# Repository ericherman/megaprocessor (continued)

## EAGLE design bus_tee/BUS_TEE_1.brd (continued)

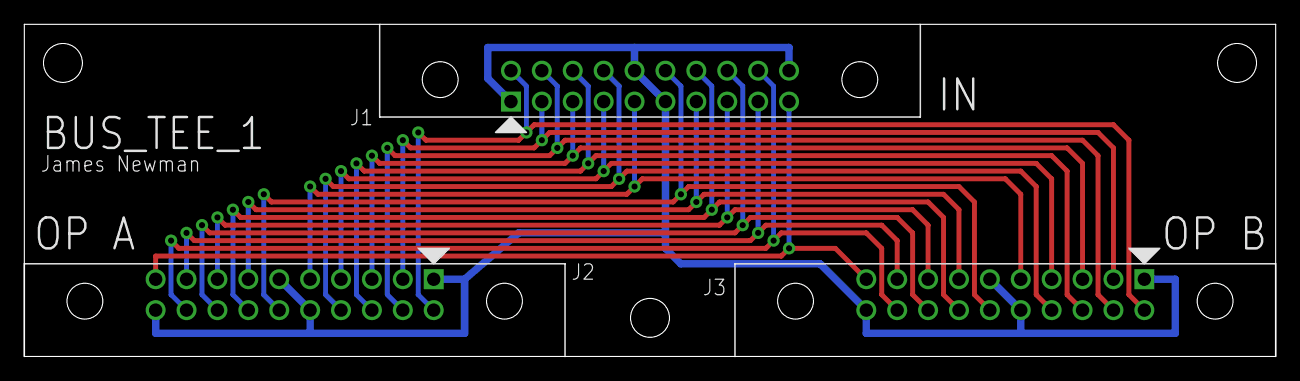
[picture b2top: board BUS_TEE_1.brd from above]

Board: 2 copper layers, 102.9 x 27.3 mm, 6 parts (0 on the bottom side), 17 nets.

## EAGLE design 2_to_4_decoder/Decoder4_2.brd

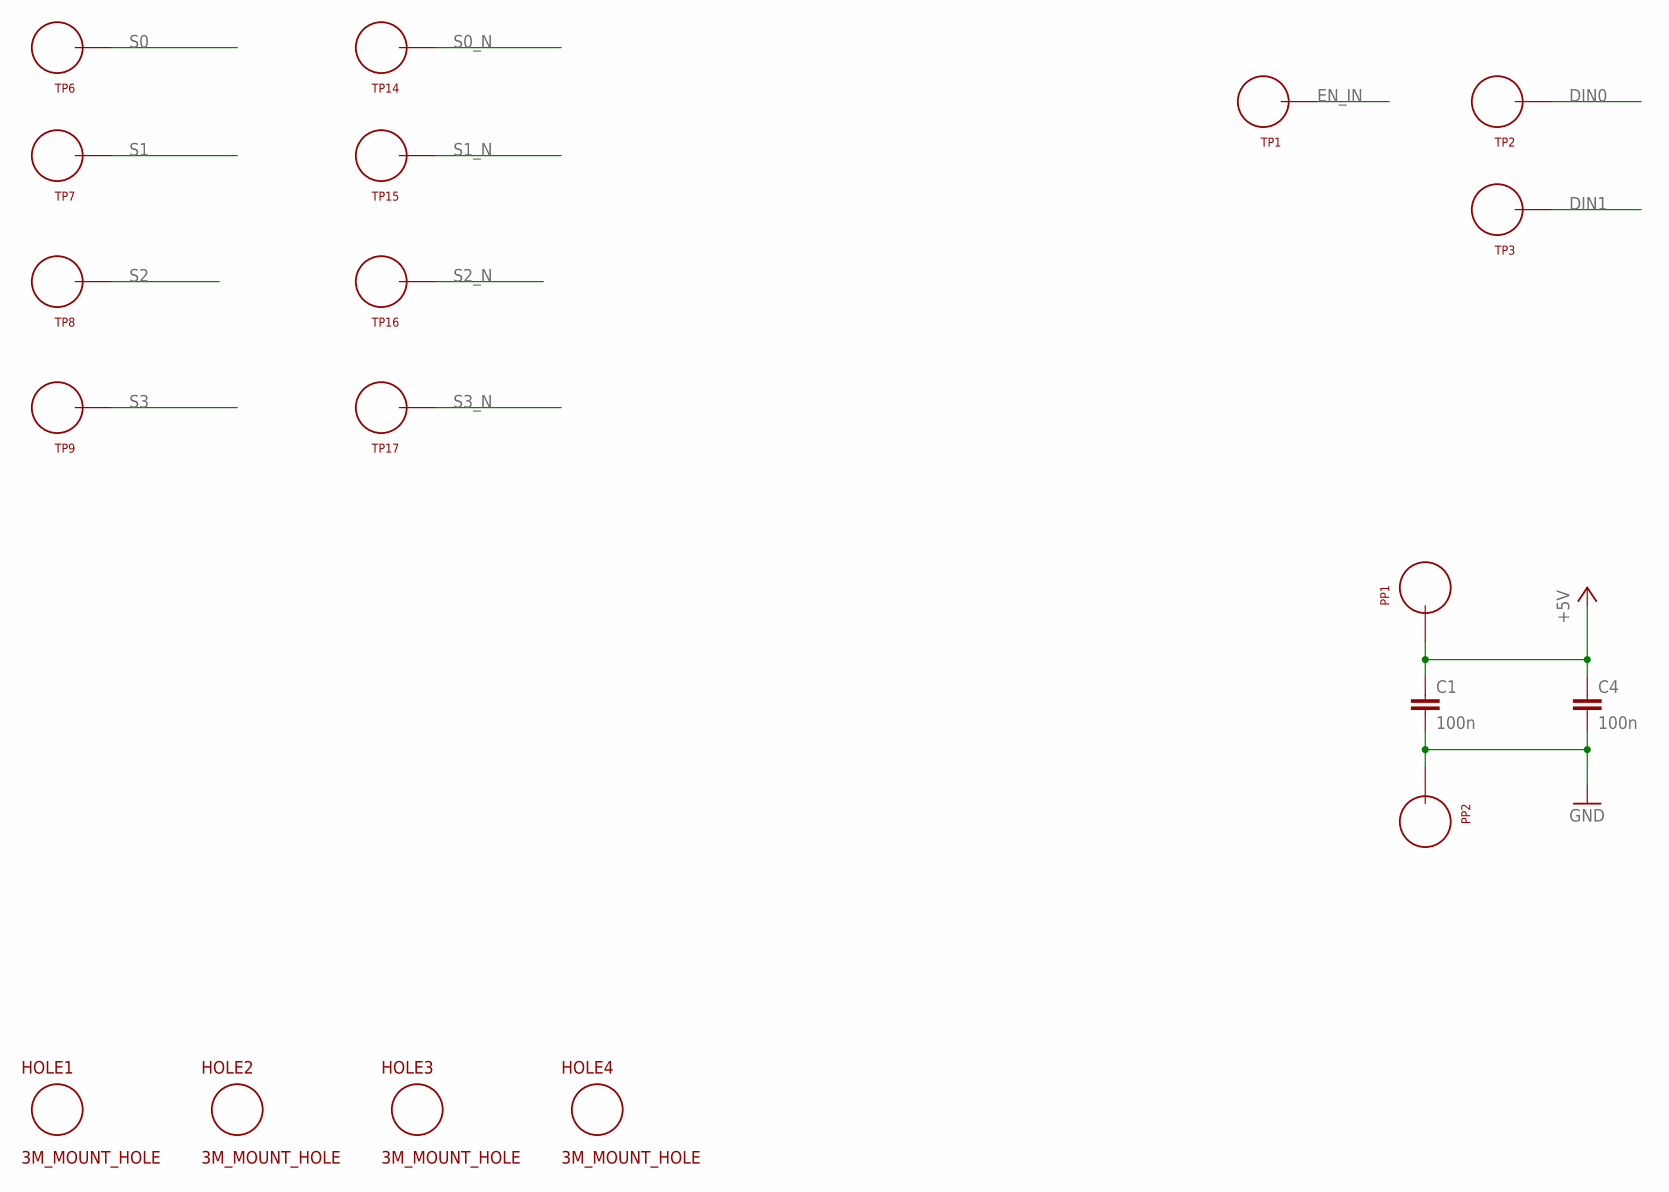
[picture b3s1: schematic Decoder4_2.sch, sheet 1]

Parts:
C1, C4: 100n; CAP_P2INCH
HOLE1, HOLE2, HOLE3, HOLE4: 3M_MOUNT_HOLE; 3M_HOLE
PP1, PP2: TEST_LOOP
TP1, TP2, TP3, TP6, TP7, TP8, TP9, TP14, TP15, TP16, TP17: TEST_LOOP

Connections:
+5V: C1.1, C4.1, PP1.P$1; also elsewhere on the board
DIN0: TP2.P$1; also elsewhere on the board
DIN1: TP3.P$1; also elsewhere on the board
EN_IN: TP1.P$1; also elsewhere on the board
GND: C1.2, C4.2, PP2.P$1; also elsewhere on the board
S0: TP6.P$1; also elsewhere on the board
S0_N: TP14.P$1; also elsewhere on the board
S1: TP7.P$1; also elsewhere on the board
S1_N: TP15.P$1; also elsewhere on the board
S2: TP8.P$1; also elsewhere on the board
S2_N: TP16.P$1; also elsewhere on the board
S3: TP9.P$1; also elsewhere on the board
S3_N: TP17.P$1; also elsewhere on the board

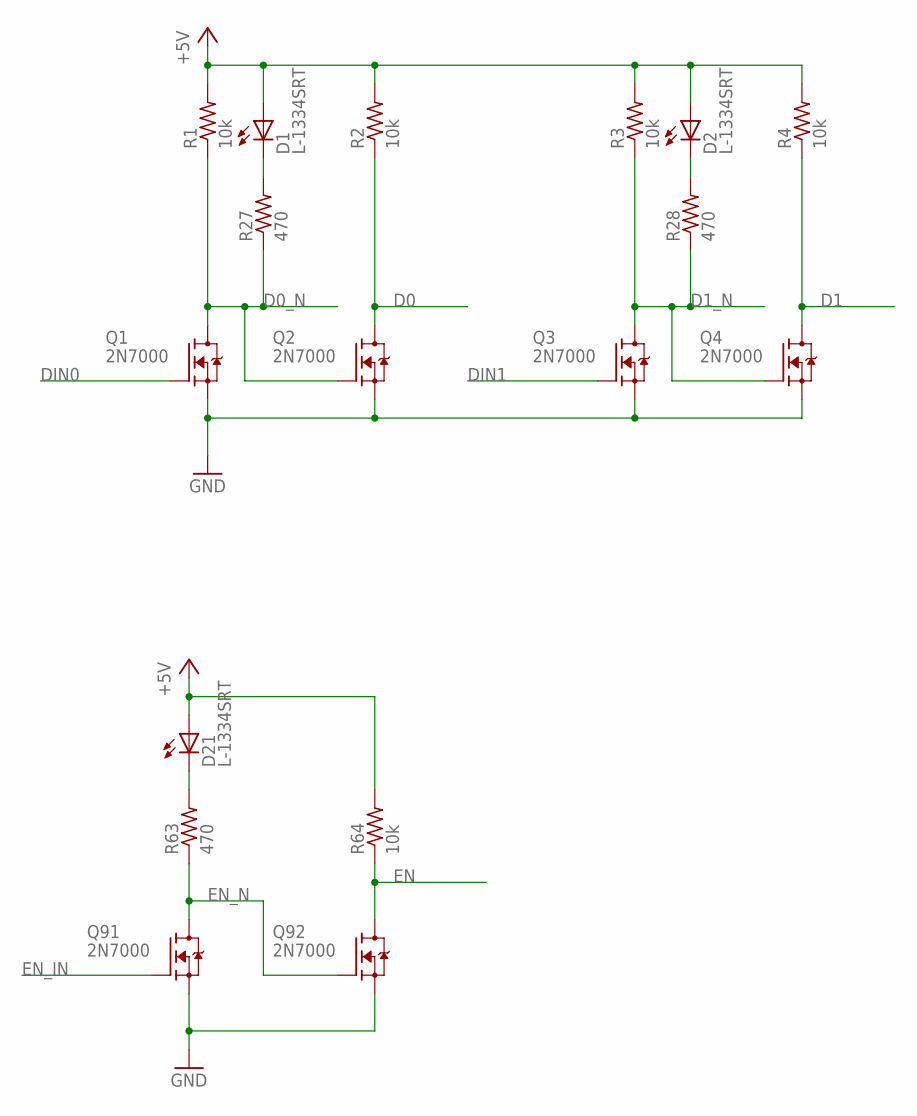
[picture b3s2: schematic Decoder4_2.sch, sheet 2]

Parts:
D1, D2, D21: L-1334SRT; LED3MM
Q1, Q2, Q3, Q4, Q91, Q92: 2N7000; TO92-DGS
R1, R2, R3, R4, R64: 10k; R_P2INCH
R27, R28, R63: 470; R_P2INCH

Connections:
+5V: D1.A, D2.A, D21.A, R1.2, R2.2, R3.2, R4.2, R64.2; also elsewhere on the board
D0: Q2.D, R2.1; also elsewhere on the board
D0_N: Q1.D, Q2.G, R1.1, R27.1; also elsewhere on the board
D1: Q4.D, R4.1; also elsewhere on the board
D1_N: Q3.D, Q4.G, R3.1, R28.1; also elsewhere on the board
DIN0: Q1.G; also elsewhere on the board
DIN1: Q3.G; also elsewhere on the board
EN: Q92.D, R64.1; also elsewhere on the board
EN_IN: Q91.G; also elsewhere on the board
EN_N: Q91.D, Q92.G, R63.1
GND: Q1.S, Q2.S, Q3.S, Q4.S, Q91.S, Q92.S; also elsewhere on the board
unnamed: D1.K (C), R27.2
unnamed: D2.K (C), R28.2
unnamed: D21.K (C), R63.2

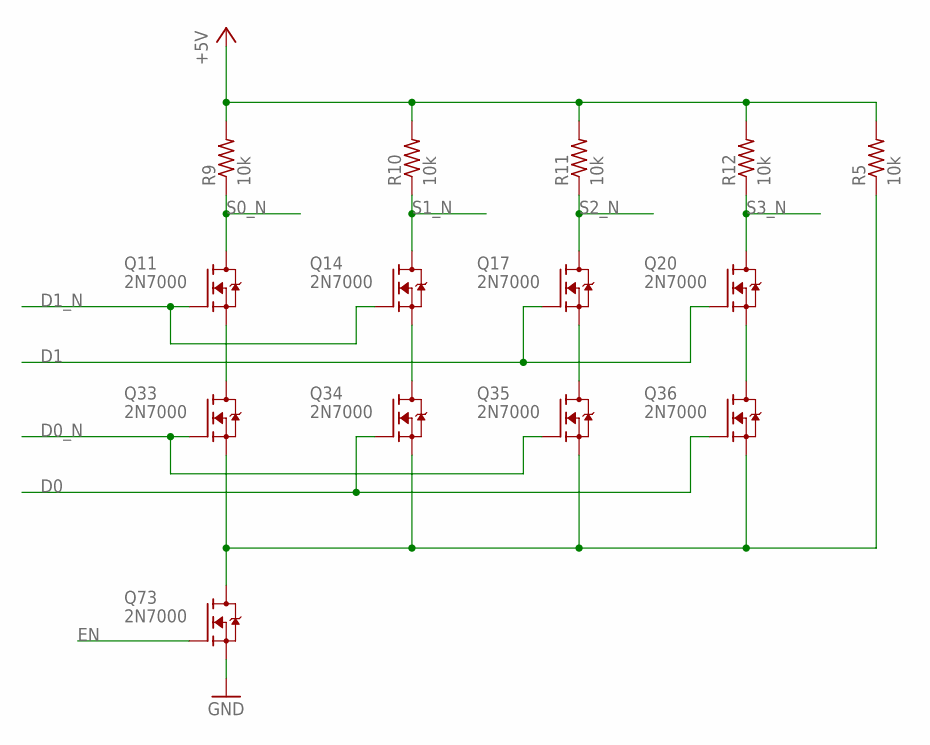
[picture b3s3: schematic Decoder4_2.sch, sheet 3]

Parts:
Q11, Q14, Q17, Q20, Q33, Q34, Q35, Q36, Q73: 2N7000; TO92-DGS
R5, R9, R10, R11, R12: 10k; R_P2INCH

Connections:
+5V: R5.2, R9.2, R10.2, R11.2, R12.2; also elsewhere on the board
D0: Q34.G, Q36.G; also elsewhere on the board
D0_N: Q33.G, Q35.G; also elsewhere on the board
D1: Q17.G, Q20.G; also elsewhere on the board
D1_N: Q11.G, Q14.G; also elsewhere on the board
EN: Q73.G; also elsewhere on the board
GND: Q73.S; also elsewhere on the board
unnamed: Q33.S, Q34.S, Q35.S, Q36.S, Q73.D, R5.1
unnamed: Q11.S, Q33.D
unnamed: Q14.S, Q34.D
unnamed: Q17.S, Q35.D
unnamed: Q20.S, Q36.D
S0_N: Q11.D, R9.1; also elsewhere on the board
S1_N: Q14.D, R10.1; also elsewhere on the board
S2_N: Q17.D, R11.1; also elsewhere on the board
S3_N: Q20.D, R12.1; also elsewhere on the board

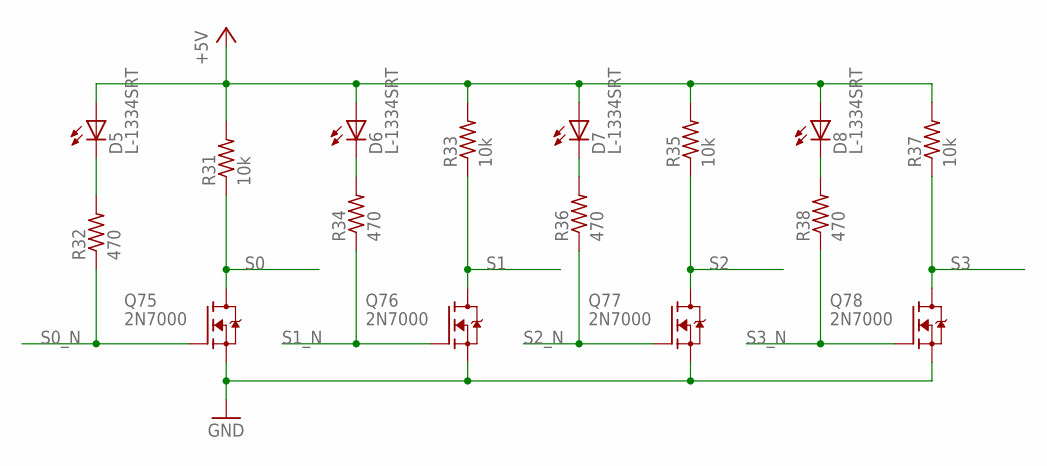
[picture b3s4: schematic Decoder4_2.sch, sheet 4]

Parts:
D5, D6, D7, D8: L-1334SRT; LED3MM
Q75, Q76, Q77, Q78: 2N7000; TO92-DGS
R31, R33, R35, R37: 10k; R_P2INCH
R32, R34, R36, R38: 470; R_P2INCH

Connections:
+5V: D5.A, D6.A, D7.A, D8.A, R31.2, R33.2, R35.2, R37.2; also elsewhere on the board
GND: Q75.S, Q76.S, Q77.S, Q78.S; also elsewhere on the board
unnamed: D5.K (C), R32.2
unnamed: D6.K (C), R34.2
unnamed: D7.K (C), R36.2
unnamed: D8.K (C), R38.2
S0: Q75.D, R31.1; also elsewhere on the board
S0_N: Q75.G, R32.1; also elsewhere on the board
S1: Q76.D, R33.1; also elsewhere on the board
S1_N: Q76.G, R34.1; also elsewhere on the board
S2: Q77.D, R35.1; also elsewhere on the board
S2_N: Q77.G, R36.1; also elsewhere on the board
S3: Q78.D, R37.1; also elsewhere on the board
S3_N: Q78.G, R38.1; also elsewhere on the board

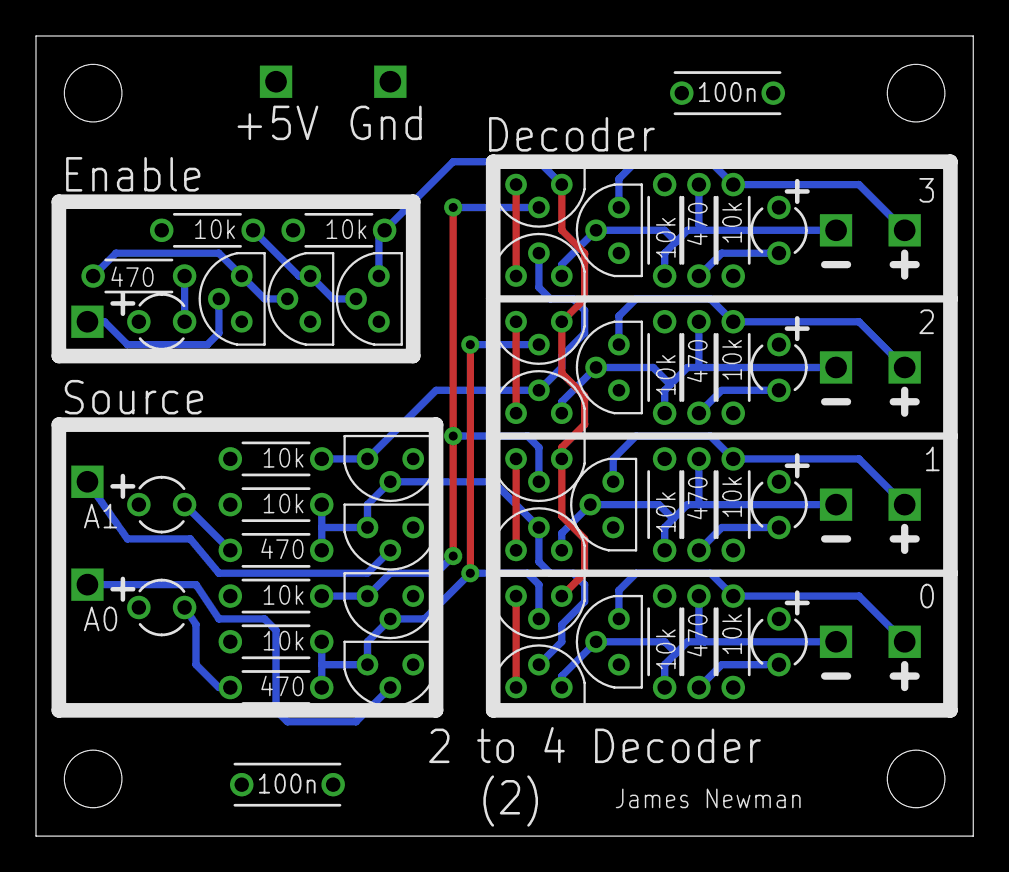
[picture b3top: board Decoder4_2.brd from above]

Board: 4 copper layers, 52.1 x 44.5 mm, 66 parts (0 on the bottom side), 31 nets.

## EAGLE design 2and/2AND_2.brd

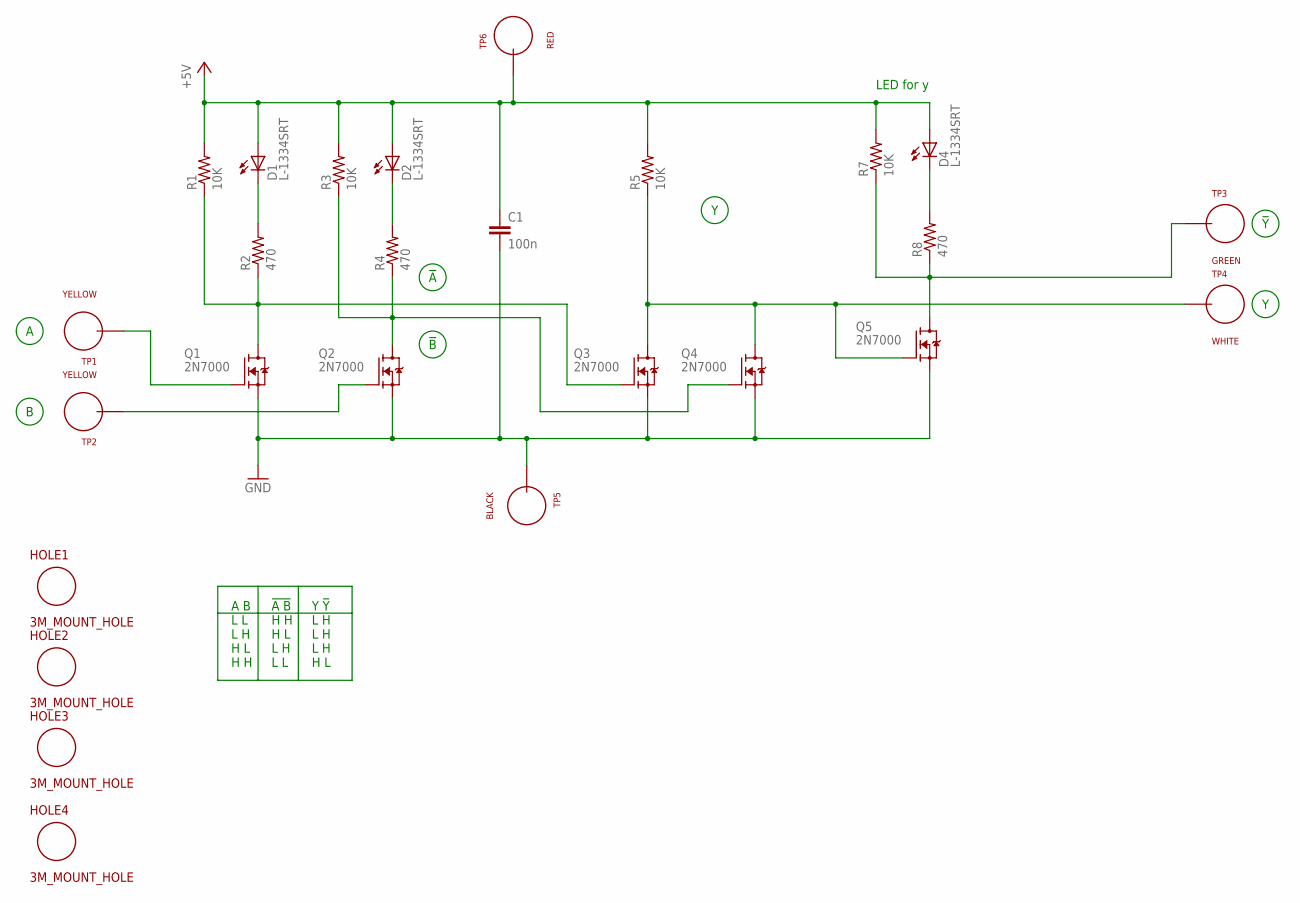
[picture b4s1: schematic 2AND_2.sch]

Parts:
C1: 100n; CAP_P2INCH
D1, D2, D4: L-1334SRT; LED3MM
HOLE1, HOLE2, HOLE3, HOLE4: 3M_MOUNT_HOLE; 3M_HOLE
Q1, Q2, Q3, Q4, Q5: 2N7000; TO92-DGS
R1, R3, R5, R7: 10K; R_P2INCH
R2, R4, R8: 470; R_P2INCH
TP1, TP2: YELLOW; TEST_LOOP
TP3: GREEN; TEST_LOOP
TP4: WHITE; TEST_LOOP
TP5: BLACK; TEST_LOOP
TP6: RED; TEST_LOOP

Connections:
+5V: C1.1, D1.A, D2.A, D4.A, R1.2, R3.2, R5.2, R7.2, TP6.P$1
GND: C1.2, Q1.S, Q2.S, Q3.S, Q4.S, Q5.S, TP5.P$1
unnamed: Q3.D, Q4.D, Q5.G, R5.1, TP4.P$1
unnamed: D4.K (C), R8.2
unnamed: Q5.D, R7.1, R8.1, TP3.P$1
unnamed: D2.K (C), R4.2
unnamed: Q2.D, Q4.G, R3.1, R4.1
unnamed: D1.K (C), R2.2
unnamed: Q1.D, Q3.G, R1.1, R2.1
unnamed: Q1.G, TP1.P$1
unnamed: Q2.G, TP2.P$1

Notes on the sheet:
A B L L L H H L H H
!A B H H H L L H L L
Y !Y L H L H L H H L
LED for y

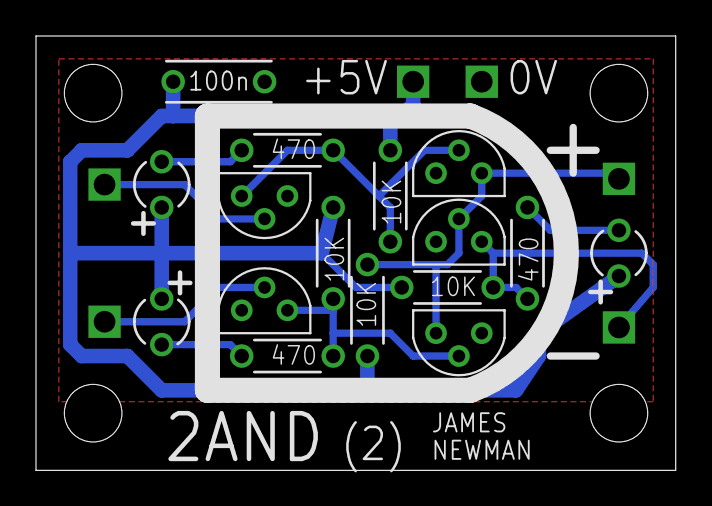
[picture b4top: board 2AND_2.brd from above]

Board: 2 copper layers, 35.5 x 24.1 mm, 26 parts (0 on the bottom side), 11 nets.

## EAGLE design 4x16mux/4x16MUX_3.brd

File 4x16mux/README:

16x4MUX

This is the most tedious to solder.

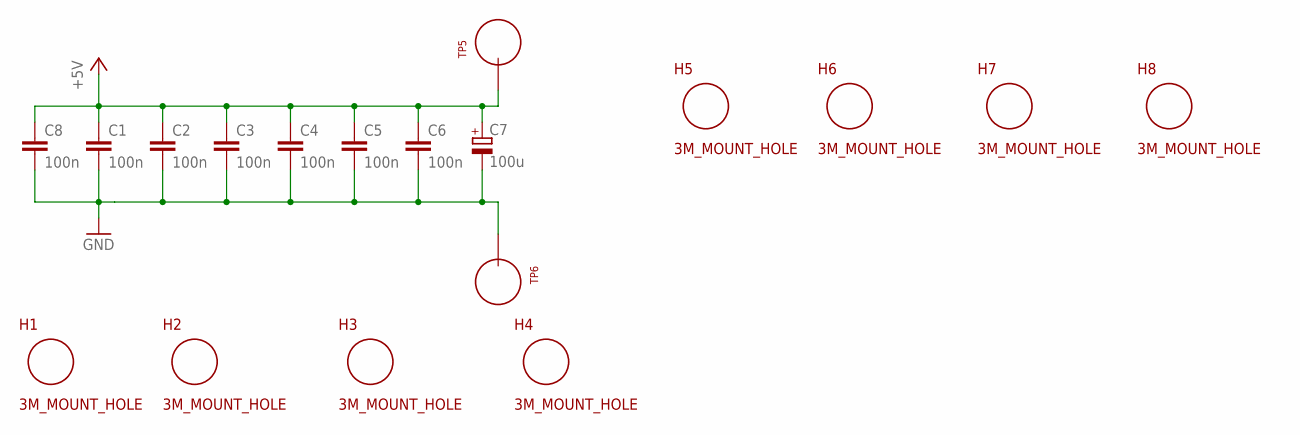
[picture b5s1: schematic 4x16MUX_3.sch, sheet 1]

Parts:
C1, C2, C3, C4, C5, C6, C8: 100n; CAP_P2INCH
C7: 100u; POLARISED_CAP_2P5_6P3MM
H1, H2, H3, H4, H5, H6, H7, H8: 3M_MOUNT_HOLE; 3M_HOLE
TP5, TP6: TEST_LOOP

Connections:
+5V: C1.1, C2.1, C3.1, C4.1, C5.1, C6.1, C7.A, C8.1, TP5.P$1; also elsewhere on the board
GND: C1.2, C2.2, C3.2, C4.2, C5.2, C6.2, C7.K, C8.2, TP6.P$1; also elsewhere on the board

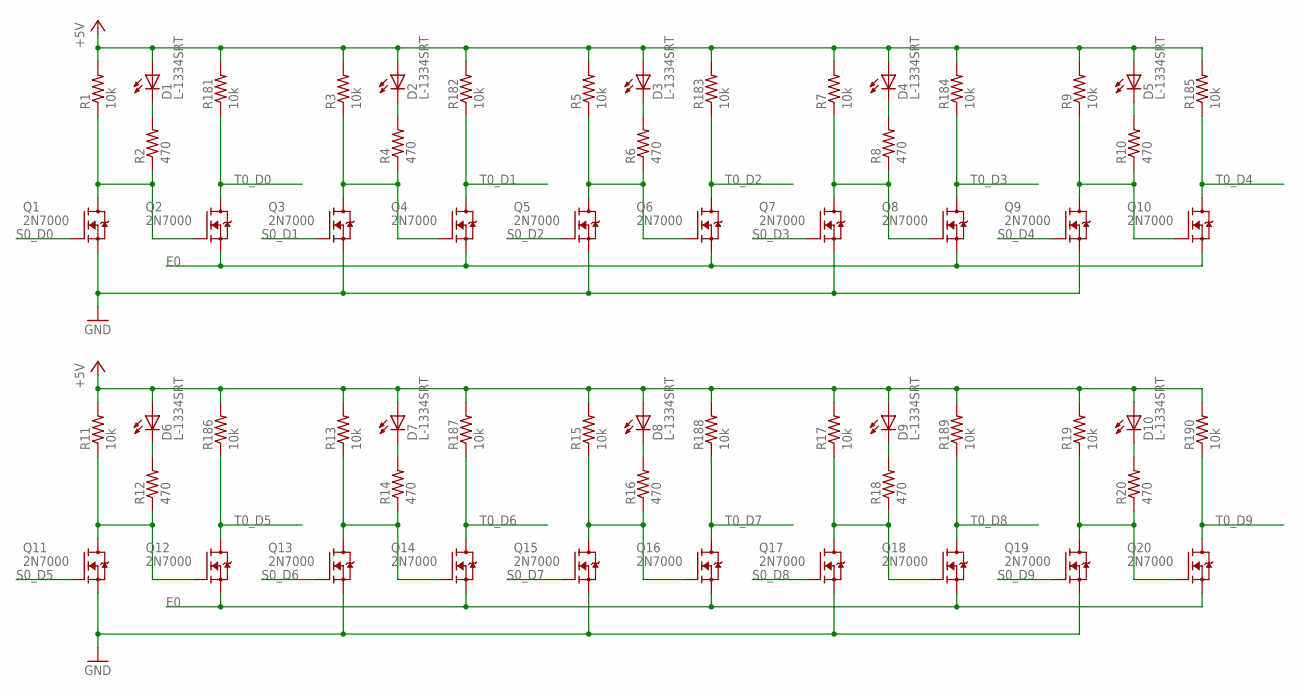
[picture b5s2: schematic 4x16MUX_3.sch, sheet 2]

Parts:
D1, D2, D3, D4, D5, D6, D7, D8, D9, D10: L-1334SRT; LED3MM
Q1, Q2, Q3, Q4, Q5, Q6, Q7, Q8, Q9, Q10, Q11, Q12, Q13, Q14, Q15, Q16, Q17, Q18, Q19, Q20: 2N7000; TO92-DGS
R1, R3, R5, R7, R9, R11, R13, R15, R17, R19, R181, R182, R183, R184, R185, R186, R187, R188, R189, R190: 10k; R_P2INCH
R2, R4, R6, R8, R10, R12, R14, R16, R18, R20: 470; R_P2INCH

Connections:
+5V: D1.A, D2.A, D3.A, D4.A, D5.A, D6.A, D7.A, D8.A, D9.A, D10.A, R1.2, R3.2, R5.2, R7.2, R9.2, R11.2, R13.2, R15.2, R17.2, R19.2, R181.2, R182.2, R183.2, R184.2, R185.2, R186.2, R187.2, R188.2, R189.2, R190.2; also elsewhere on the board
E0: Q2.S, Q4.S, Q6.S, Q8.S, Q10.S, Q12.S, Q14.S, Q16.S, Q18.S, Q20.S; also elsewhere on the board
GND: Q1.S, Q3.S, Q5.S, Q7.S, Q9.S, Q11.S, Q13.S, Q15.S, Q17.S, Q19.S; also elsewhere on the board
unnamed: Q3.D, Q4.G, R3.1, R4.1
unnamed: Q1.D, Q2.G, R1.1, R2.1
unnamed: D1.K (C), R2.2
unnamed: D2.K (C), R4.2
unnamed: Q5.D, Q6.G, R5.1, R6.1
unnamed: D3.K (C), R6.2
unnamed: Q7.D, Q8.G, R7.1, R8.1
unnamed: D4.K (C), R8.2
unnamed: Q9.D, Q10.G, R9.1, R10.1
unnamed: D5.K (C), R10.2
unnamed: Q11.D, Q12.G, R11.1, R12.1
unnamed: D6.K (C), R12.2
unnamed: Q13.D, Q14.G, R13.1, R14.1
unnamed: D7.K (C), R14.2
unnamed: Q15.D, Q16.G, R15.1, R16.1
unnamed: D8.K (C), R16.2
unnamed: Q17.D, Q18.G, R17.1, R18.1
unnamed: D9.K (C), R18.2
unnamed: Q19.D, Q20.G, R19.1, R20.1
unnamed: D10.K (C), R20.2
S0_D0: Q1.G; also elsewhere on the board
S0_D1: Q3.G; also elsewhere on the board
S0_D2: Q5.G; also elsewhere on the board
S0_D3: Q7.G; also elsewhere on the board
S0_D4: Q9.G; also elsewhere on the board
S0_D5: Q11.G; also elsewhere on the board
S0_D6: Q13.G; also elsewhere on the board
S0_D7: Q15.G; also elsewhere on the board
S0_D8: Q17.G; also elsewhere on the board
S0_D9: Q19.G; also elsewhere on the board
T0_D0: Q2.D, R181.1; also elsewhere on the board
T0_D1: Q4.D, R182.1; also elsewhere on the board
T0_D2: Q6.D, R183.1; also elsewhere on the board
T0_D3: Q8.D, R184.1; also elsewhere on the board
T0_D4: Q10.D, R185.1; also elsewhere on the board
T0_D5: Q12.D, R186.1; also elsewhere on the board
T0_D6: Q14.D, R187.1; also elsewhere on the board
T0_D7: Q16.D, R188.1; also elsewhere on the board
T0_D8: Q18.D, R189.1; also elsewhere on the board
T0_D9: Q20.D, R190.1; also elsewhere on the board

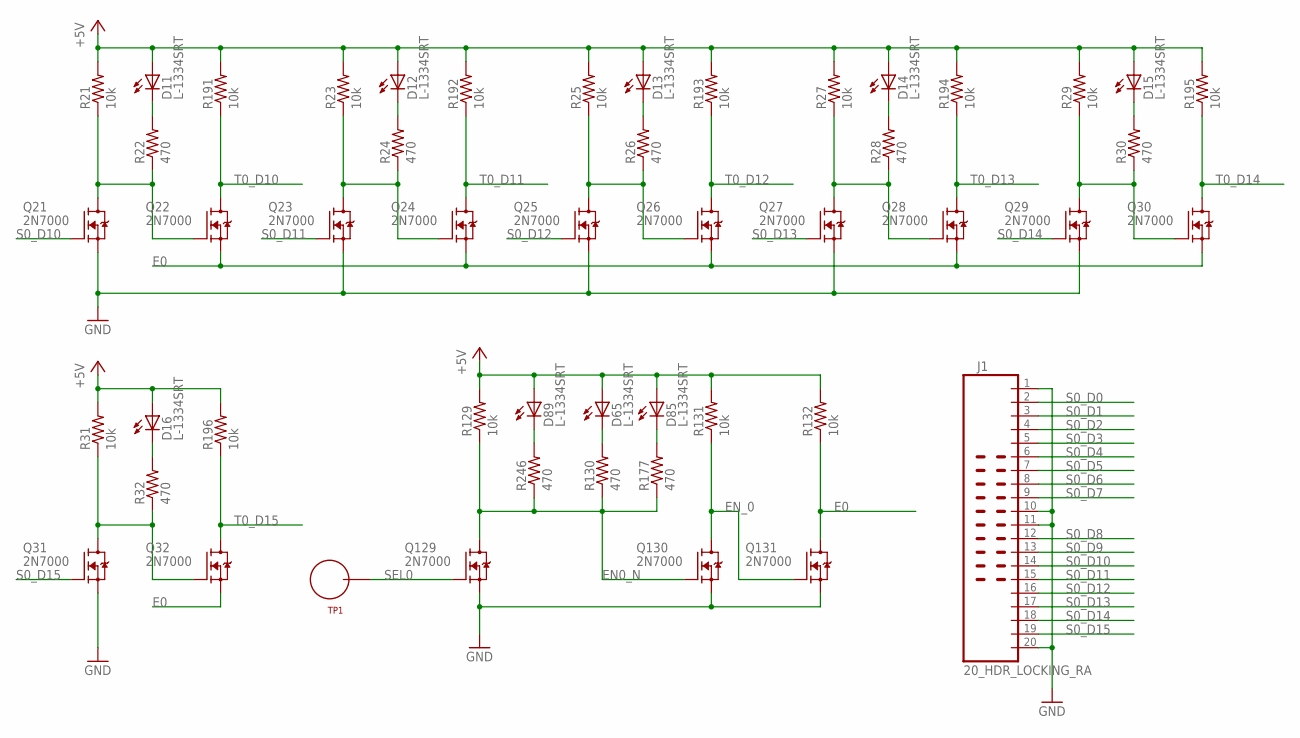
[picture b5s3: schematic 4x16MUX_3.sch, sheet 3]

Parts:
D11, D12, D13, D14, D15, D16, D65, D85, D89: L-1334SRT; LED3MM
J1: 20_HDR_LOCKING_RA
Q21, Q22, Q23, Q24, Q25, Q26, Q27, Q28, Q29, Q30, Q31, Q32, Q129, Q130, Q131: 2N7000; TO92-DGS
R21, R23, R25, R27, R29, R31, R129, R131, R132, R191, R192, R193, R194, R195, R196: 10k; R_P2INCH
R22, R24, R26, R28, R30, R32, R130, R177, R246: 470; R_P2INCH
TP1: TEST_LOOP

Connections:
+5V: D11.A, D12.A, D13.A, D14.A, D15.A, D16.A, D65.A, D85.A, D89.A, R21.2, R23.2, R25.2, R27.2, R29.2, R31.2, R129.2, R131.2, R132.2, R191.2, R192.2, R193.2, R194.2, R195.2, R196.2; also elsewhere on the board
E0: Q22.S, Q24.S, Q26.S, Q28.S, Q30.S, Q32.S, Q131.D, R132.1; also elsewhere on the board
EN0_N: Q129.D, Q130.G, R129.1, R130.1, R177.1, R246.1; also elsewhere on the board
EN_0: Q130.D, Q131.G, R131.1
GND: J1.1, J1.10, J1.11, J1.20, Q21.S, Q23.S, Q25.S, Q27.S, Q29.S, Q31.S, Q129.S, Q130.S, Q131.S; also elsewhere on the board
unnamed: Q21.D, Q22.G, R21.1, R22.1
unnamed: D11.K (C), R22.2
unnamed: Q23.D, Q24.G, R23.1, R24.1
unnamed: D12.K (C), R24.2
unnamed: Q25.D, Q26.G, R25.1, R26.1
unnamed: D13.K (C), R26.2
unnamed: Q27.D, Q28.G, R27.1, R28.1
unnamed: D14.K (C), R28.2
unnamed: Q29.D, Q30.G, R29.1, R30.1
unnamed: D15.K (C), R30.2
unnamed: Q31.D, Q32.G, R31.1, R32.1
unnamed: D16.K (C), R32.2
unnamed: D65.K (C), R130.2
unnamed: D85.K (C), R177.2
unnamed: D89.K (C), R246.2
S0_D0: J1.2; also elsewhere on the board
S0_D1: J1.3; also elsewhere on the board
S0_D2: J1.4; also elsewhere on the board
S0_D3: J1.5; also elsewhere on the board
S0_D4: J1.6; also elsewhere on the board
S0_D5: J1.7; also elsewhere on the board
S0_D6: J1.8; also elsewhere on the board
S0_D7: J1.9; also elsewhere on the board
S0_D8: J1.12; also elsewhere on the board
S0_D9: J1.13; also elsewhere on the board
S0_D10: J1.14, Q21.G
S0_D11: J1.15, Q23.G
S0_D12: J1.16, Q25.G
S0_D13: J1.17, Q27.G
S0_D14: J1.18, Q29.G
S0_D15: J1.19, Q31.G
SEL0: Q129.G, TP1.P$1
T0_D10: Q22.D, R191.1; also elsewhere on the board
T0_D11: Q24.D, R192.1; also elsewhere on the board
T0_D12: Q26.D, R193.1; also elsewhere on the board
T0_D13: Q28.D, R194.1; also elsewhere on the board
T0_D14: Q30.D, R195.1; also elsewhere on the board
T0_D15: Q32.D, R196.1; also elsewhere on the board

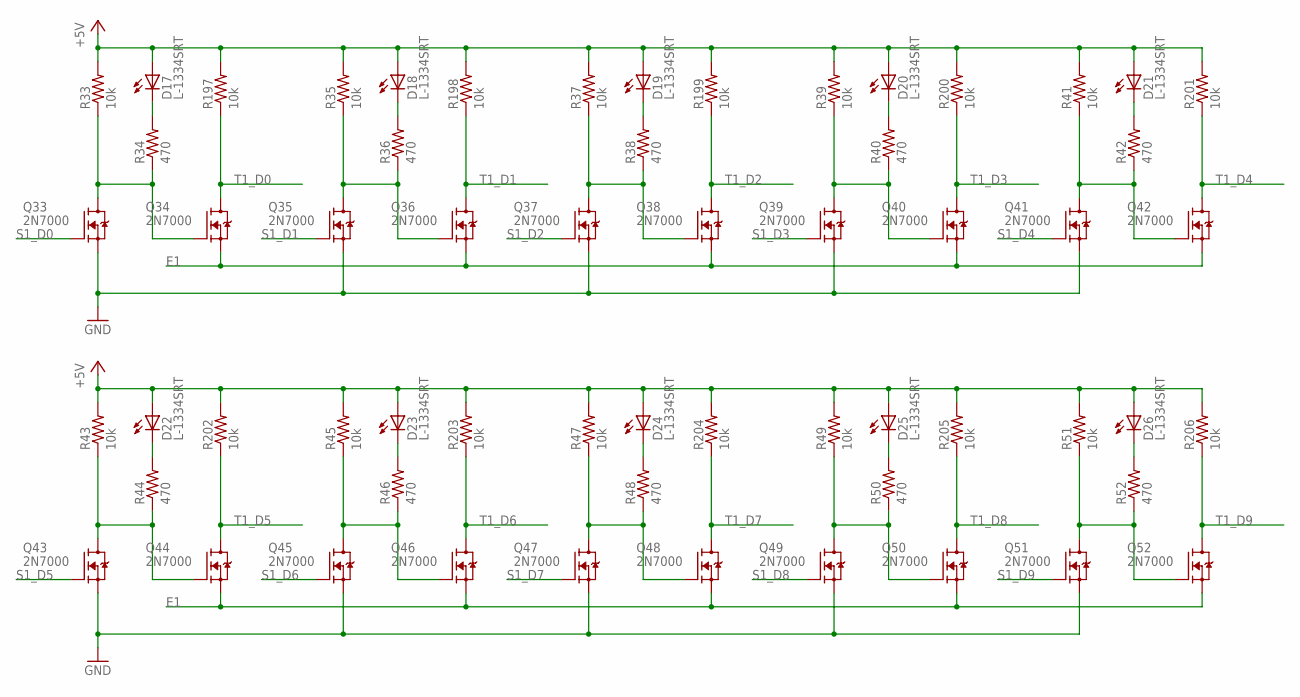
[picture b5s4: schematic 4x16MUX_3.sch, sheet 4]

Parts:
D17, D18, D19, D20, D21, D22, D23, D24, D25, D26: L-1334SRT; LED3MM
Q33, Q34, Q35, Q36, Q37, Q38, Q39, Q40, Q41, Q42, Q43, Q44, Q45, Q46, Q47, Q48, Q49, Q50, Q51, Q52: 2N7000; TO92-DGS
R33, R35, R37, R39, R41, R43, R45, R47, R49, R51, R197, R198, R199, R200, R201, R202, R203, R204, R205, R206: 10k; R_P2INCH
R34, R36, R38, R40, R42, R44, R46, R48, R50, R52: 470; R_P2INCH

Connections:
+5V: D17.A, D18.A, D19.A, D20.A, D21.A, D22.A, D23.A, D24.A, D25.A, D26.A, R33.2, R35.2, R37.2, R39.2, R41.2, R43.2, R45.2, R47.2, R49.2, R51.2, R197.2, R198.2, R199.2, R200.2, R201.2, R202.2, R203.2, R204.2, R205.2, R206.2; also elsewhere on the board
E1: Q34.S, Q36.S, Q38.S, Q40.S, Q42.S, Q44.S, Q46.S, Q48.S, Q50.S, Q52.S; also elsewhere on the board
GND: Q33.S, Q35.S, Q37.S, Q39.S, Q41.S, Q43.S, Q45.S, Q47.S, Q49.S, Q51.S; also elsewhere on the board
unnamed: Q33.D, Q34.G, R33.1, R34.1
unnamed: D17.K (C), R34.2
unnamed: Q35.D, Q36.G, R35.1, R36.1
unnamed: D18.K (C), R36.2
unnamed: Q37.D, Q38.G, R37.1, R38.1
unnamed: D19.K (C), R38.2
unnamed: Q39.D, Q40.G, R39.1, R40.1
unnamed: D20.K (C), R40.2
unnamed: Q41.D, Q42.G, R41.1, R42.1
unnamed: D21.K (C), R42.2
unnamed: Q43.D, Q44.G, R43.1, R44.1
unnamed: D22.K (C), R44.2
unnamed: Q45.D, Q46.G, R45.1, R46.1
unnamed: D23.K (C), R46.2
unnamed: Q47.D, Q48.G, R47.1, R48.1
unnamed: D24.K (C), R48.2
unnamed: Q49.D, Q50.G, R49.1, R50.1
unnamed: D25.K (C), R50.2
unnamed: Q51.D, Q52.G, R51.1, R52.1
unnamed: D26.K (C), R52.2
S1_D0: Q33.G; also elsewhere on the board
S1_D1: Q35.G; also elsewhere on the board
S1_D2: Q37.G; also elsewhere on the board
S1_D3: Q39.G; also elsewhere on the board
S1_D4: Q41.G; also elsewhere on the board
S1_D5: Q43.G; also elsewhere on the board
S1_D6: Q45.G; also elsewhere on the board
S1_D7: Q47.G; also elsewhere on the board
S1_D8: Q49.G; also elsewhere on the board
S1_D9: Q51.G; also elsewhere on the board
T1_D0: Q34.D, R197.1; also elsewhere on the board
T1_D1: Q36.D, R198.1; also elsewhere on the board
T1_D2: Q38.D, R199.1; also elsewhere on the board
T1_D3: Q40.D, R200.1; also elsewhere on the board
T1_D4: Q42.D, R201.1; also elsewhere on the board
T1_D5: Q44.D, R202.1; also elsewhere on the board
T1_D6: Q46.D, R203.1; also elsewhere on the board
T1_D7: Q48.D, R204.1; also elsewhere on the board
T1_D8: Q50.D, R205.1; also elsewhere on the board
T1_D9: Q52.D, R206.1; also elsewhere on the board

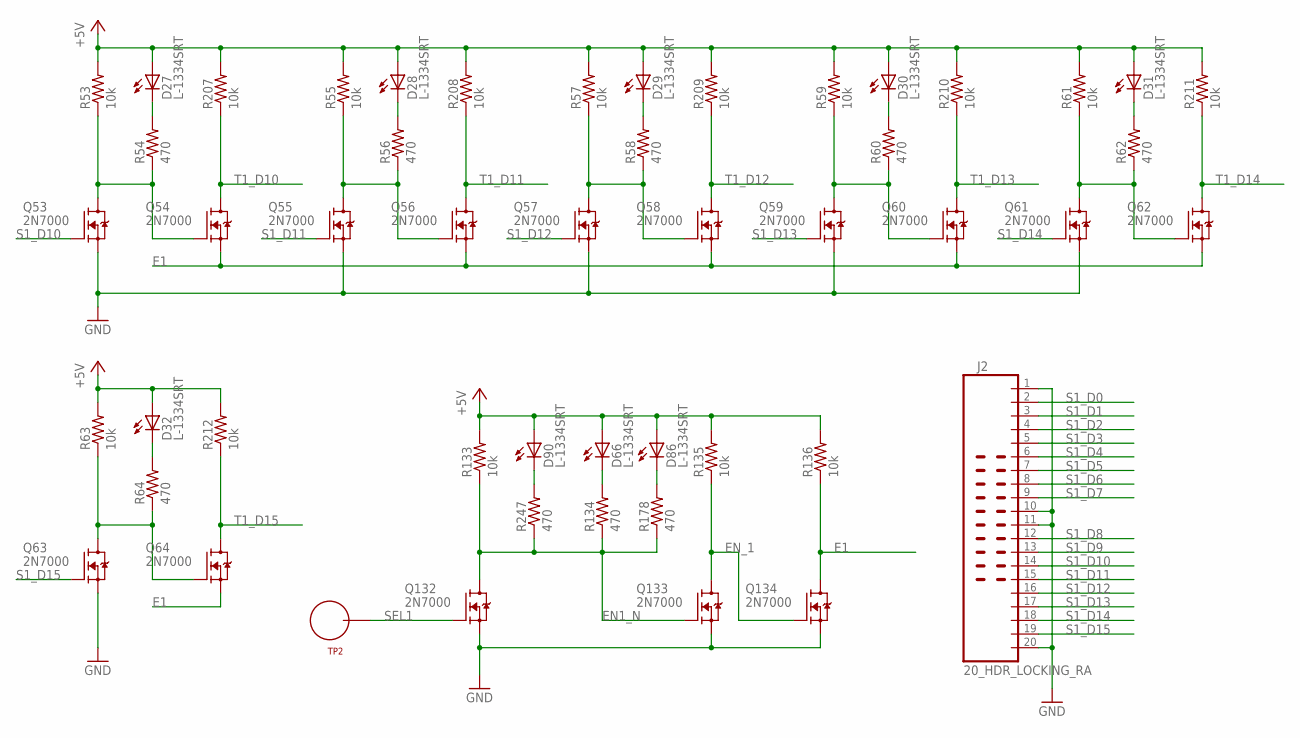
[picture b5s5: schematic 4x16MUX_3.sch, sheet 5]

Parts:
D27, D28, D29, D30, D31, D32, D66, D86, D90: L-1334SRT; LED3MM
J2: 20_HDR_LOCKING_RA
Q53, Q54, Q55, Q56, Q57, Q58, Q59, Q60, Q61, Q62, Q63, Q64, Q132, Q133, Q134: 2N7000; TO92-DGS
R53, R55, R57, R59, R61, R63, R133, R135, R136, R207, R208, R209, R210, R211, R212: 10k; R_P2INCH
R54, R56, R58, R60, R62, R64, R134, R178, R247: 470; R_P2INCH
TP2: TEST_LOOP

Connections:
+5V: D27.A, D28.A, D29.A, D30.A, D31.A, D32.A, D66.A, D86.A, D90.A, R53.2, R55.2, R57.2, R59.2, R61.2, R63.2, R133.2, R135.2, R136.2, R207.2, R208.2, R209.2, R210.2, R211.2, R212.2; also elsewhere on the board
E1: Q54.S, Q56.S, Q58.S, Q60.S, Q62.S, Q64.S, Q134.D, R136.1; also elsewhere on the board
EN1_N: Q132.D, Q133.G, R133.1, R134.1, R178.1, R247.1; also elsewhere on the board
EN_1: Q133.D, Q134.G, R135.1
GND: J2.1, J2.10, J2.11, J2.20, Q53.S, Q55.S, Q57.S, Q59.S, Q61.S, Q63.S, Q132.S, Q133.S, Q134.S; also elsewhere on the board
unnamed: Q53.D, Q54.G, R53.1, R54.1
unnamed: D27.K (C), R54.2
unnamed: Q55.D, Q56.G, R55.1, R56.1
unnamed: D28.K (C), R56.2
unnamed: Q57.D, Q58.G, R57.1, R58.1
unnamed: D29.K (C), R58.2
unnamed: Q59.D, Q60.G, R59.1, R60.1
unnamed: D30.K (C), R60.2
unnamed: Q61.D, Q62.G, R61.1, R62.1
unnamed: D31.K (C), R62.2
unnamed: Q63.D, Q64.G, R63.1, R64.1
unnamed: D32.K (C), R64.2
unnamed: D66.K (C), R134.2
unnamed: D86.K (C), R178.2
unnamed: D90.K (C), R247.2
S1_D0: J2.2; also elsewhere on the board
S1_D1: J2.3; also elsewhere on the board
S1_D2: J2.4; also elsewhere on the board
S1_D3: J2.5; also elsewhere on the board
S1_D4: J2.6; also elsewhere on the board
S1_D5: J2.7; also elsewhere on the board
S1_D6: J2.8; also elsewhere on the board
S1_D7: J2.9; also elsewhere on the board
S1_D8: J2.12; also elsewhere on the board
S1_D9: J2.13; also elsewhere on the board
S1_D10: J2.14, Q53.G
S1_D11: J2.15, Q55.G
S1_D12: J2.16, Q57.G
S1_D13: J2.17, Q59.G
S1_D14: J2.18, Q61.G
S1_D15: J2.19, Q63.G
SEL1: Q132.G, TP2.P$1
T1_D10: Q54.D, R207.1; also elsewhere on the board
T1_D11: Q56.D, R208.1; also elsewhere on the board
T1_D12: Q58.D, R209.1; also elsewhere on the board
T1_D13: Q60.D, R210.1; also elsewhere on the board
T1_D14: Q62.D, R211.1; also elsewhere on the board
T1_D15: Q64.D, R212.1; also elsewhere on the board

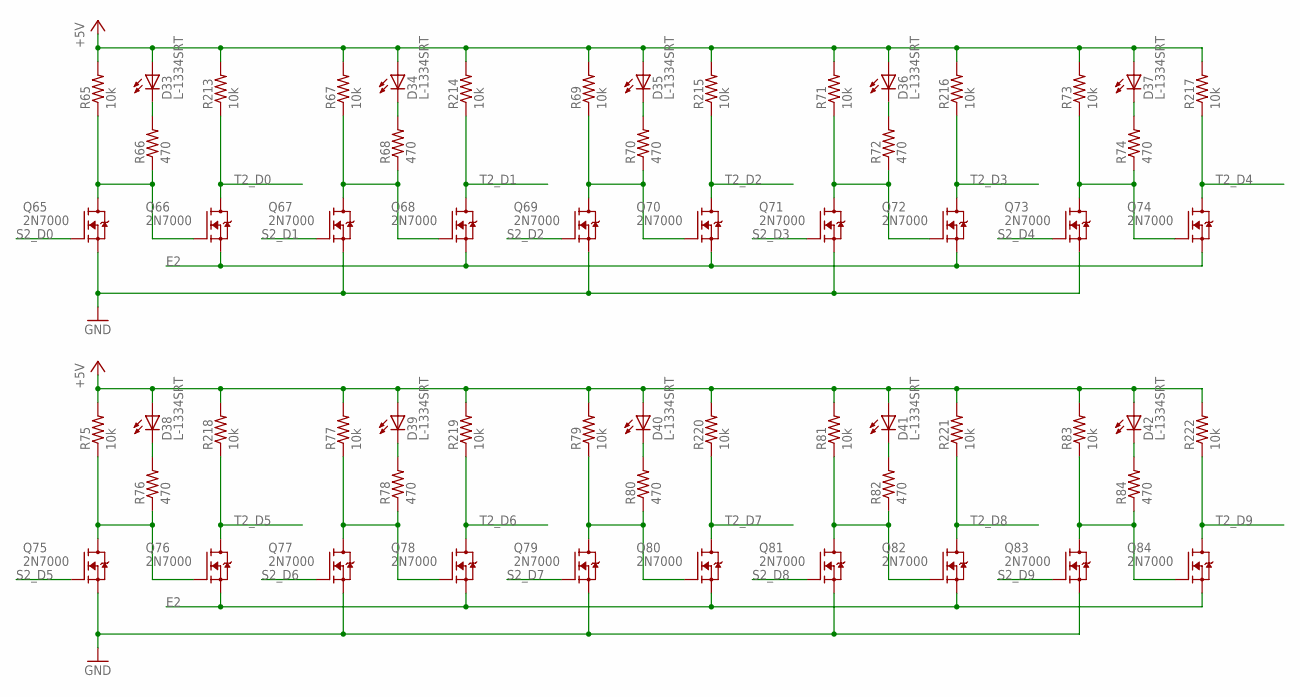
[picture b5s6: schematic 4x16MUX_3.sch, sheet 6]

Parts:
D33, D34, D35, D36, D37, D38, D39, D40, D41, D42: L-1334SRT; LED3MM
Q65, Q66, Q67, Q68, Q69, Q70, Q71, Q72, Q73, Q74, Q75, Q76, Q77, Q78, Q79, Q80, Q81, Q82, Q83, Q84: 2N7000; TO92-DGS
R65, R67, R69, R71, R73, R75, R77, R79, R81, R83, R213, R214, R215, R216, R217, R218, R219, R220, R221, R222: 10k; R_P2INCH
R66, R68, R70, R72, R74, R76, R78, R80, R82, R84: 470; R_P2INCH

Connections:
+5V: D33.A, D34.A, D35.A, D36.A, D37.A, D38.A, D39.A, D40.A, D41.A, D42.A, R65.2, R67.2, R69.2, R71.2, R73.2, R75.2, R77.2, R79.2, R81.2, R83.2, R213.2, R214.2, R215.2, R216.2, R217.2, R218.2, R219.2, R220.2, R221.2, R222.2; also elsewhere on the board
E2: Q66.S, Q68.S, Q70.S, Q72.S, Q74.S, Q76.S, Q78.S, Q80.S, Q82.S, Q84.S; also elsewhere on the board
GND: Q65.S, Q67.S, Q69.S, Q71.S, Q73.S, Q75.S, Q77.S, Q79.S, Q81.S, Q83.S; also elsewhere on the board
unnamed: Q65.D, Q66.G, R65.1, R66.1
unnamed: D33.K (C), R66.2
unnamed: Q67.D, Q68.G, R67.1, R68.1
unnamed: D34.K (C), R68.2
unnamed: Q69.D, Q70.G, R69.1, R70.1
unnamed: D35.K (C), R70.2
unnamed: Q71.D, Q72.G, R71.1, R72.1
unnamed: D36.K (C), R72.2
unnamed: Q73.D, Q74.G, R73.1, R74.1
unnamed: D37.K (C), R74.2
unnamed: Q75.D, Q76.G, R75.1, R76.1
unnamed: D38.K (C), R76.2
unnamed: Q77.D, Q78.G, R77.1, R78.1
unnamed: D39.K (C), R78.2
unnamed: Q79.D, Q80.G, R79.1, R80.1
unnamed: D40.K (C), R80.2
unnamed: Q81.D, Q82.G, R81.1, R82.1
unnamed: D41.K (C), R82.2
unnamed: Q83.D, Q84.G, R83.1, R84.1
unnamed: D42.K (C), R84.2
S2_D0: Q65.G; also elsewhere on the board
S2_D1: Q67.G; also elsewhere on the board
S2_D2: Q69.G; also elsewhere on the board
S2_D3: Q71.G; also elsewhere on the board
S2_D4: Q73.G; also elsewhere on the board
S2_D5: Q75.G; also elsewhere on the board
S2_D6: Q77.G; also elsewhere on the board
S2_D7: Q79.G; also elsewhere on the board
S2_D8: Q81.G; also elsewhere on the board
S2_D9: Q83.G; also elsewhere on the board
T2_D0: Q66.D, R213.1; also elsewhere on the board
T2_D1: Q68.D, R214.1; also elsewhere on the board
T2_D2: Q70.D, R215.1; also elsewhere on the board
T2_D3: Q72.D, R216.1; also elsewhere on the board
T2_D4: Q74.D, R217.1; also elsewhere on the board
T2_D5: Q76.D, R218.1; also elsewhere on the board
T2_D6: Q78.D, R219.1; also elsewhere on the board
T2_D7: Q80.D, R220.1; also elsewhere on the board
T2_D8: Q82.D, R221.1; also elsewhere on the board
T2_D9: Q84.D, R222.1; also elsewhere on the board
